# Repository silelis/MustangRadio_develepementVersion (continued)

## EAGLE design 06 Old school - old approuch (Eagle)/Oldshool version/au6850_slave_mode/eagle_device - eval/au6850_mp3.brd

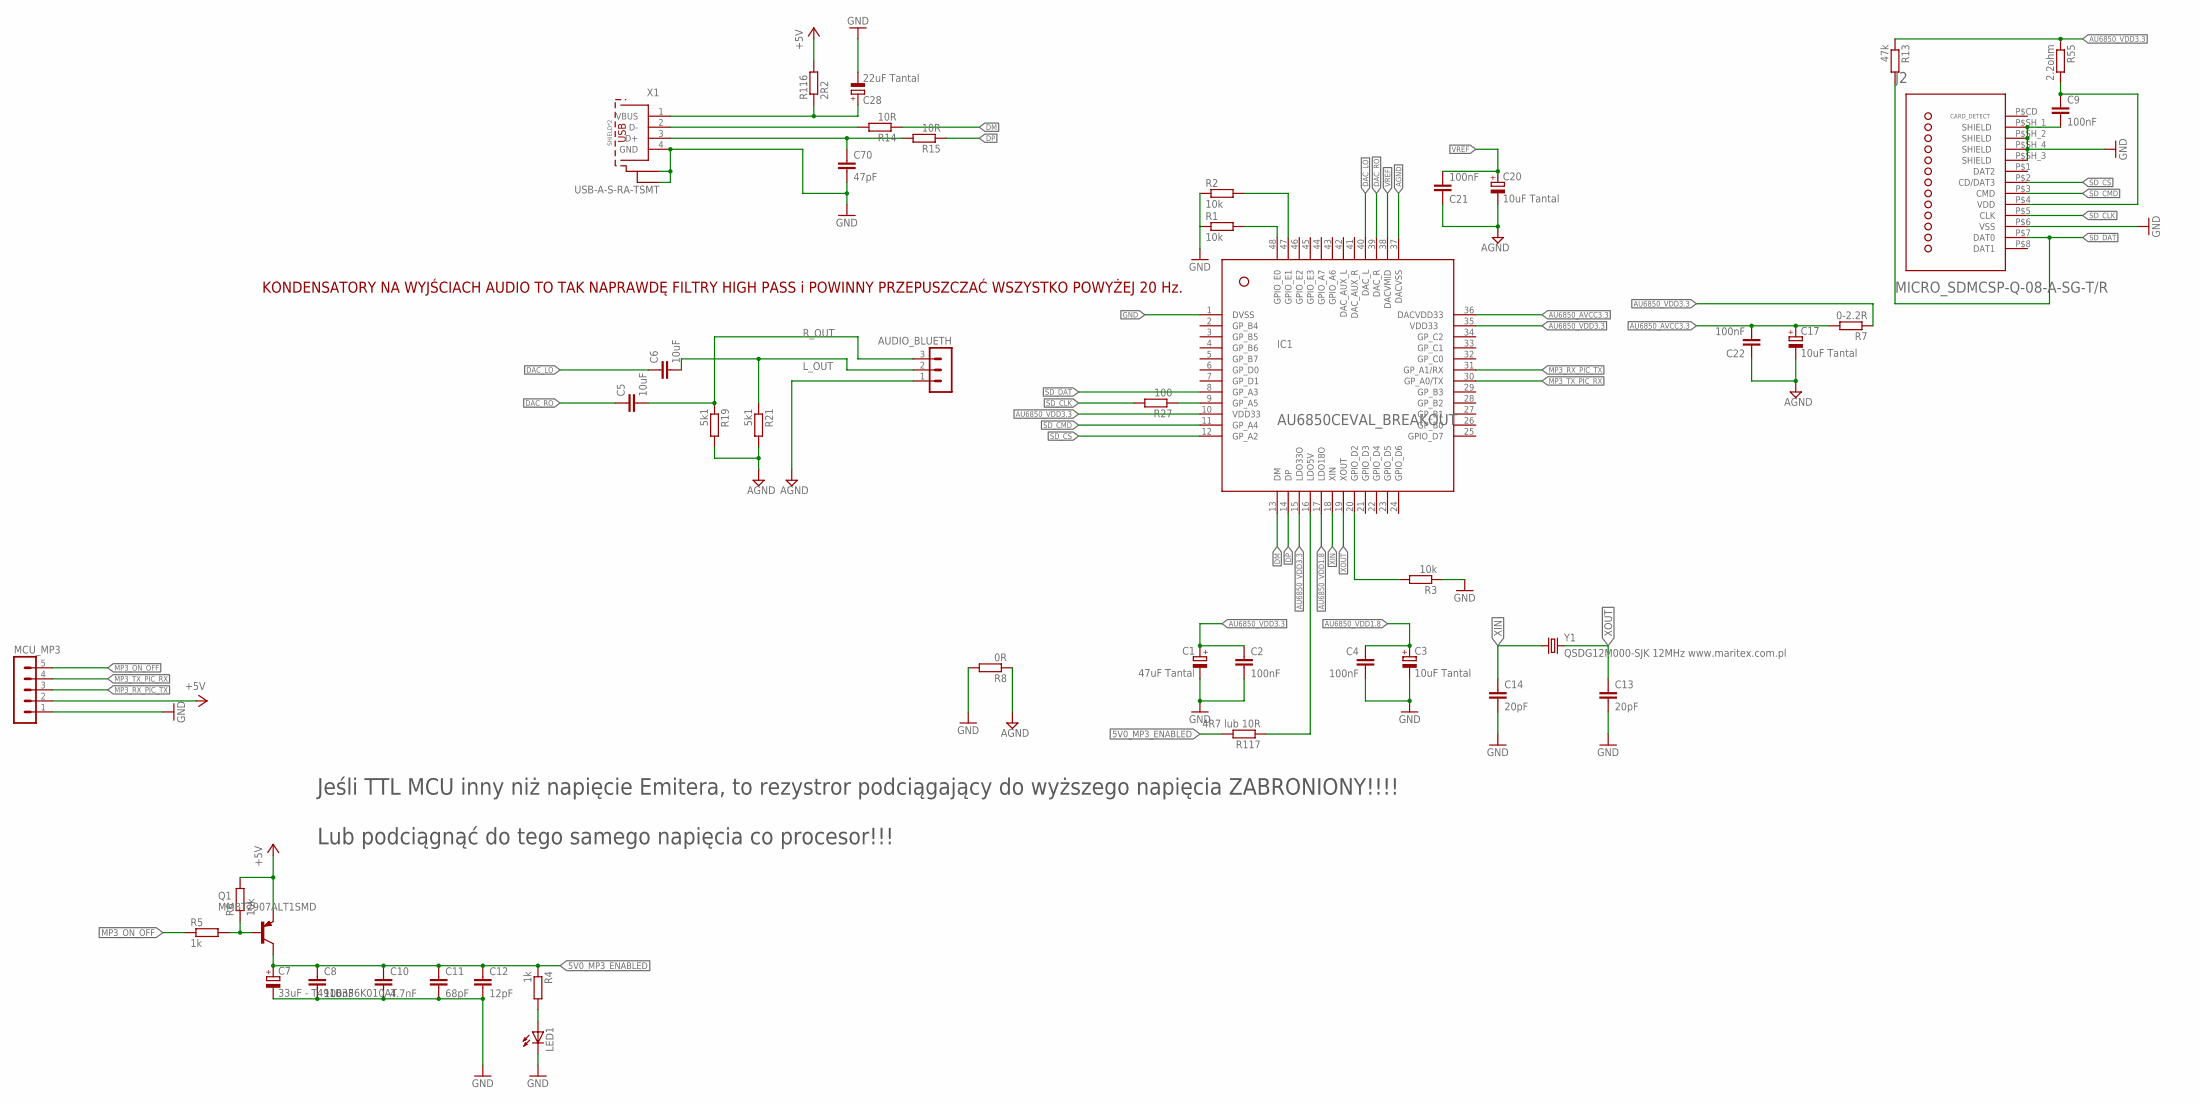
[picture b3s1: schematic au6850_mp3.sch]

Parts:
AUDIO_BLUETH: MA03-1
C1: 47uF Tantal; B/3528-21R; PARTNUM TAJB476K010R
C2, C4, C8, C9, C21, C22: 100nF; C0805
C3: 10uF Tantal; B/3528-21R; PARTNUM TAJA106K010R
C5, C6: 10uF; C0805
C7: 33uF - T491B336K010AT; SMC_B; PARTNUM TAJB336K010R
C10: 4.7nF; C0805
C11: 68pF; C0805
C12: 12pF; C0603K
C13, C14: 20pF; C0805
C17, C20: 10uF Tantal; B/3528-21R
C28: 22uF Tantal; SMC_B; PARTNUM TAJB226M010R
C70: 47pF; C0805
IC1: AU6850CEVAL_BREAKOUT; LQFP48-7BREAKOUT
J2: MICRO_SDMCSP-Q-08-A-SG-T/R; MICRO_SD_8PINS; PARTNUM MCSP-Q-08-A-SG-T/R
LED1: LED3MM
MCU_MP3: MA05-1
Q1: MMBT2907ALT1SMD; SOT23-BEC
R1, R2, R3: 10k; R0805
R4, R5: 1k; M0805
R6: 10k; M0805
R7: 0-2.2R; R0805
R8: 0R; R0805
R13: 47k; R0805
R14, R15: 10R; R0805
R19, R21: 5k1; R0805
R27: 100; R0805
R55: 2.2ohm; R0805
R116: 2R2; R0805
R117: 4R7 lub 10R; R0805
X1: USB-A-S-RA-TSMT
Y1: QSDG12M000-SJK 12MHz www.maritex.com.pl; HC49UP; PARTNUM 12.00M-SMDHC49S

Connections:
5V0_MP3_ENABLED: C7.+, C8.1, C10.1, C11.1, C12.1, Q1.C, R4.1, R117.2
+5V: MCU_MP3.2, Q1.E, R6.2, R116.2
AGND: AUDIO_BLUETH.1, C17.-, C20.-, C21.1, C22.1, IC1.37 (DACVSS), R8.1, R19.2, R21.2
AU6850_AVCC3.3: C17.+, C22.2, IC1.36 (DACVDD33), R7.2
AU6850_VDD1.8: C3.+, C4.1, IC1.17 (LDO18O)
AU6850_VDD3.3: C1.+, C2.1, IC1.10 (VDD33), IC1.15 (LDO33O), IC1.35 (VDD33), R7.1, R13.1, R55.1
DAC_LO: C6.1, IC1.40 (DAC_L)
DAC_RO: C5.1, IC1.39 (DAC_R)
DM: IC1.13 (DM), R14.1
DP: IC1.14 (DP), R15.1
GND: C1.-, C2.2, C3.-, C4.2, C7.-, C8.2, C9.2, C10.2, C11.2, C12.2, C13.2, C14.2, C28.-, C70.2, IC1.1 (DVSS), J2.P$6 (VSS), J2.P$SH_1 (1_GND_PAD), J2.P$SH_2 (2_GND_PAD), J2.P$SH_3 (3_GND_PAD), J2.P$SH_4 (4_GND_PAD), LED1.K (C), MCU_MP3.1, R1.1, R2.1, R3.1, R8.2, X1.4 (GND), X1.5 (SH1), X1.6 (SH2)
L_OUT: AUDIO_BLUETH.2, C6.2, R21.1
MP3_ON_OFF: MCU_MP3.5, R5.1
MP3_RX_PIC_TX: IC1.31 (GP_A1/RX), MCU_MP3.3
MP3_TX_PIC_RX: IC1.30 (GP_A0/TX), MCU_MP3.4
unnamed: LED1.A, R4.2
unnamed: Q1.B, R5.2, R6.1
unnamed: IC1.16 (LDO5V), R117.1
unnamed: IC1.9 (GP_A5), R27.1
unnamed: C28.+, R116.1, X1.1 (VBUS)
unnamed: C70.1, R15.2, X1.3 (D+)
unnamed: R14.2, X1.2 (D-)
unnamed: C9.1, J2.P$4 (VDD), R55.2
R_OUT: AUDIO_BLUETH.3, C5.2, R19.1
SD_CLK: J2.P$5 (CLK), R27.2
SD_CMD: IC1.11 (GP_A4), J2.P$3 (CMD)
SD_CS: IC1.12 (GP_A2), J2.P$2 (CD/DAT3)
SD_DAT: IC1.8 (GP_A3), J2.P$7 (DAT0), R13.2
SLAVE_D2: IC1.20 (GPIO_D2), R3.2
SLAVE_E0: IC1.48 (GPIO_E0), R1.2
SLAVE_E1: IC1.47 (GPIO_E1), R2.2
VREF: C20.+, C21.2, IC1.38 (DACVMID)
XIN: C14.1, IC1.18 (XIN), Y1.1
XOUT: C13.1, IC1.19 (XOUT), Y1.2

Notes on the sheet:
KONDENSATORY NA WYJŚCIACH AUDIO TO TAK NAPRAWDĘ FILTRY HIGH PASS i POWINNY PRZEPUSZCZAĆ WSZYSTKO POWYŻEJ 20 Hz.
Jeśli TTL MCU inny niż napięcie Emitera, to rezystror podciągający do wyższego napięcia ZABRONIONY!!!! Lub podciągnąć do tego samego napięcia co procesor!!!

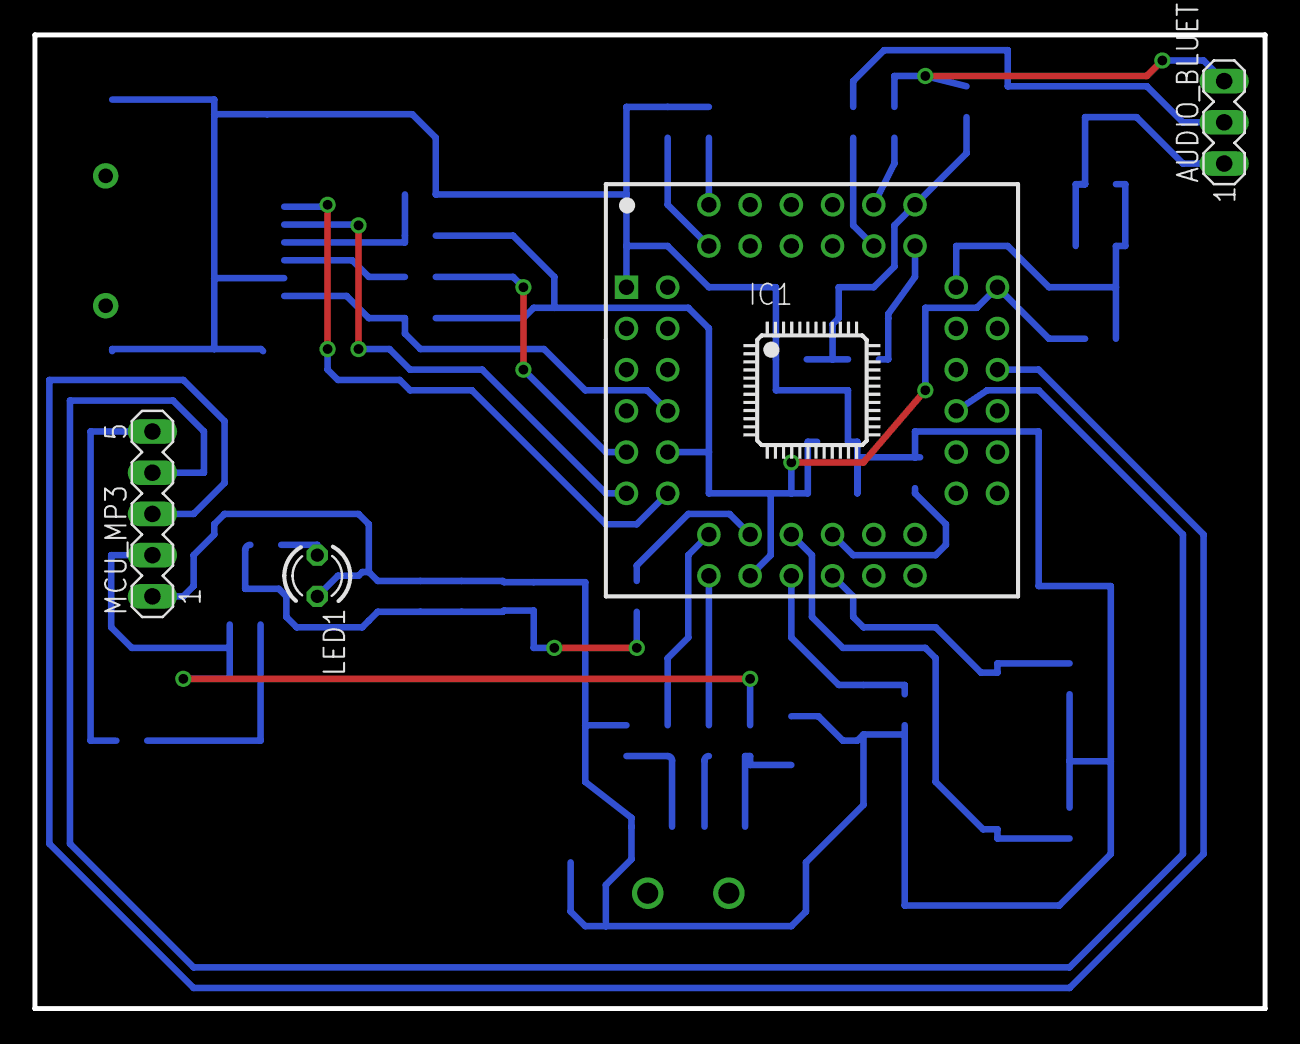
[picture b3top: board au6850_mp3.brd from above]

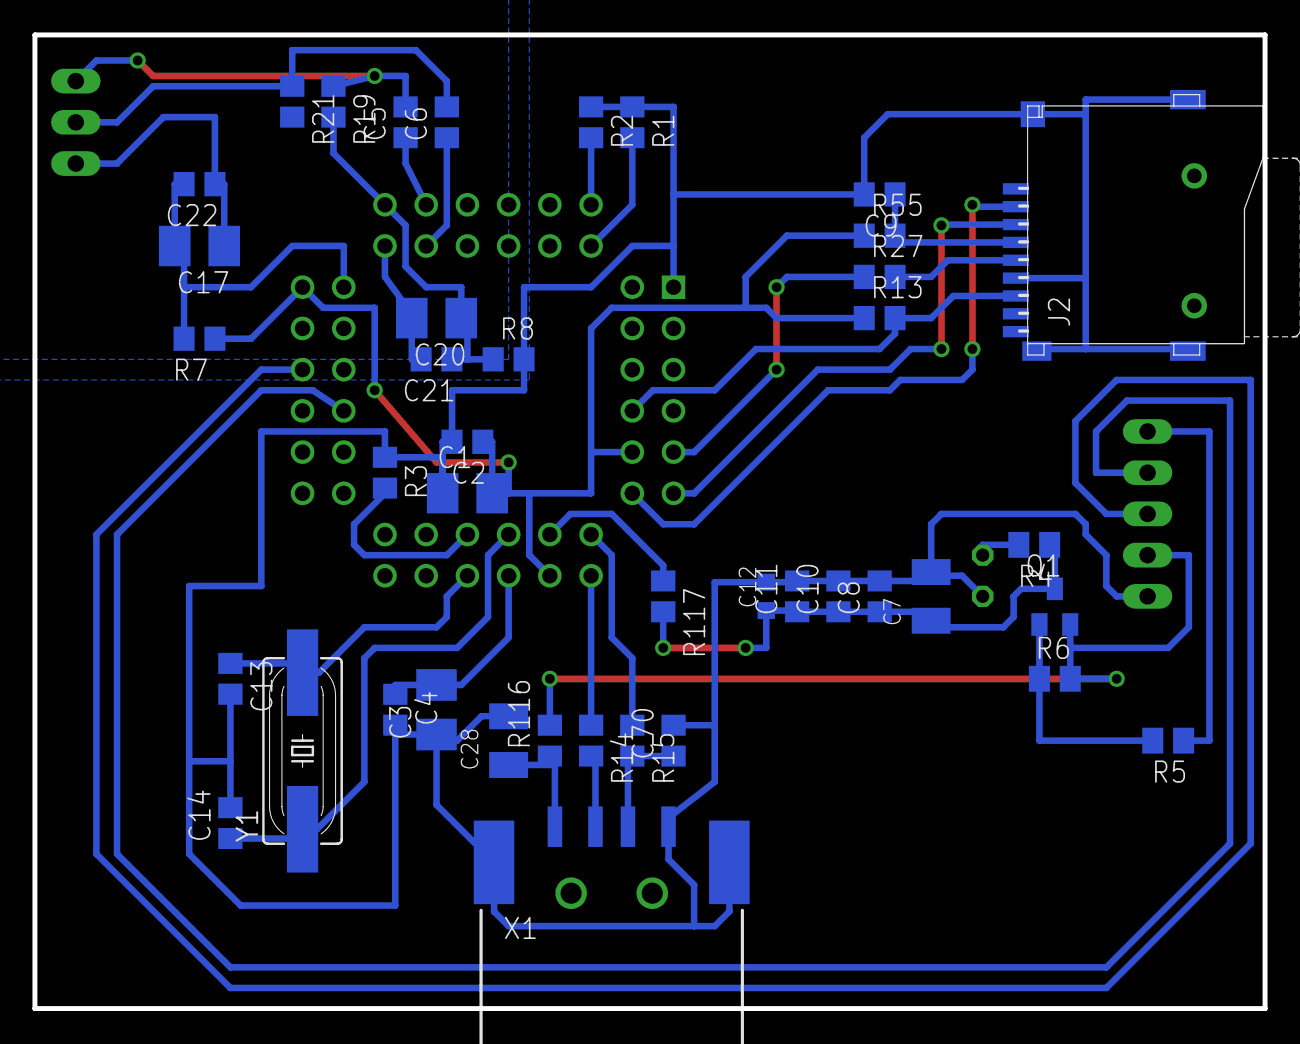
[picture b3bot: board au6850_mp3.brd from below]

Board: 2 copper layers, 75.8 x 60.0 mm, 45 parts (41 on the bottom side), 34 nets.

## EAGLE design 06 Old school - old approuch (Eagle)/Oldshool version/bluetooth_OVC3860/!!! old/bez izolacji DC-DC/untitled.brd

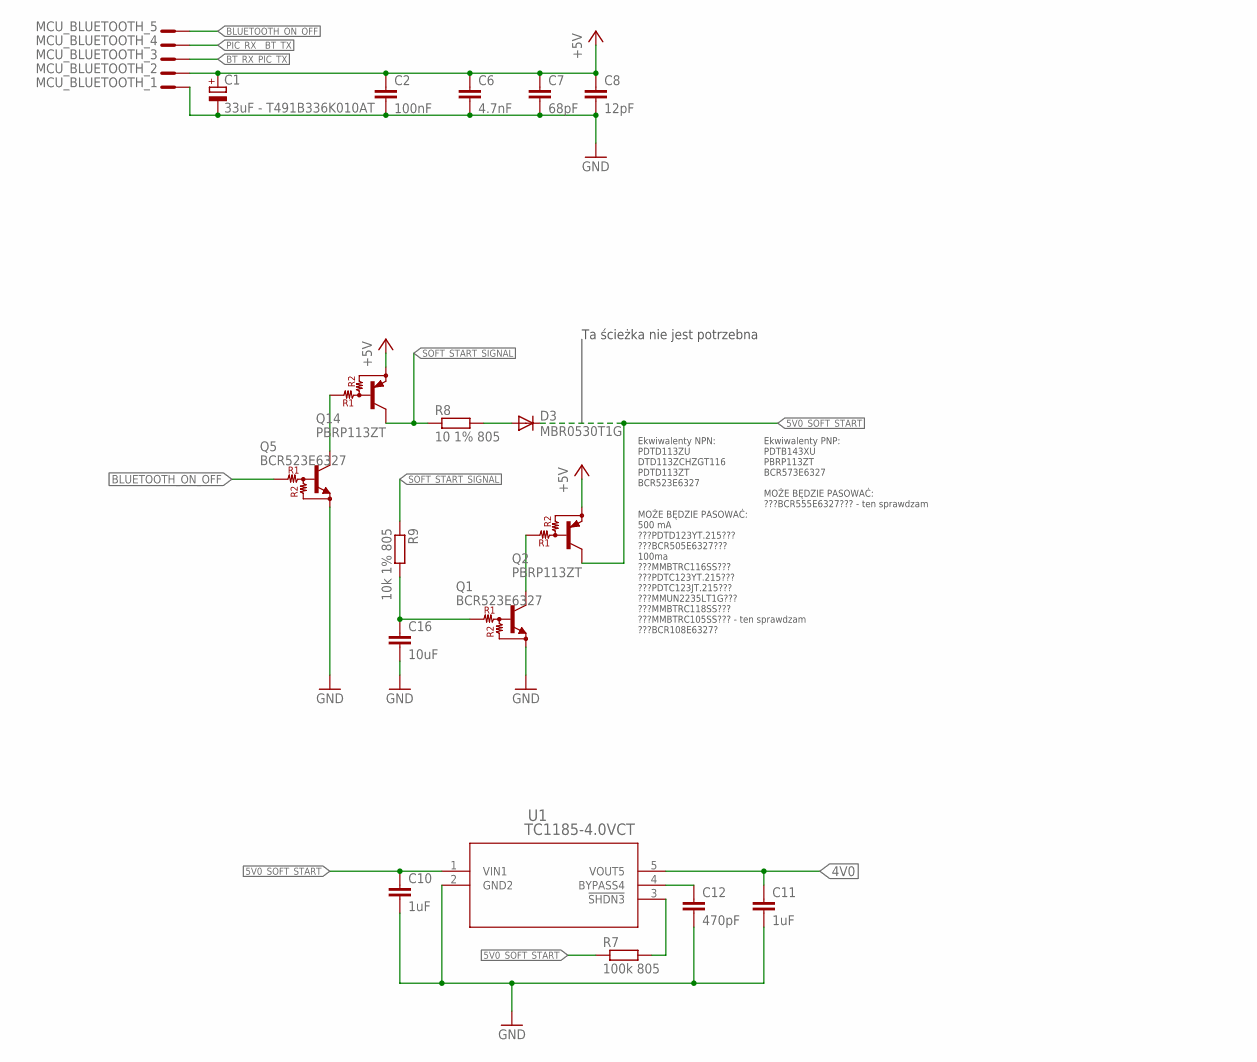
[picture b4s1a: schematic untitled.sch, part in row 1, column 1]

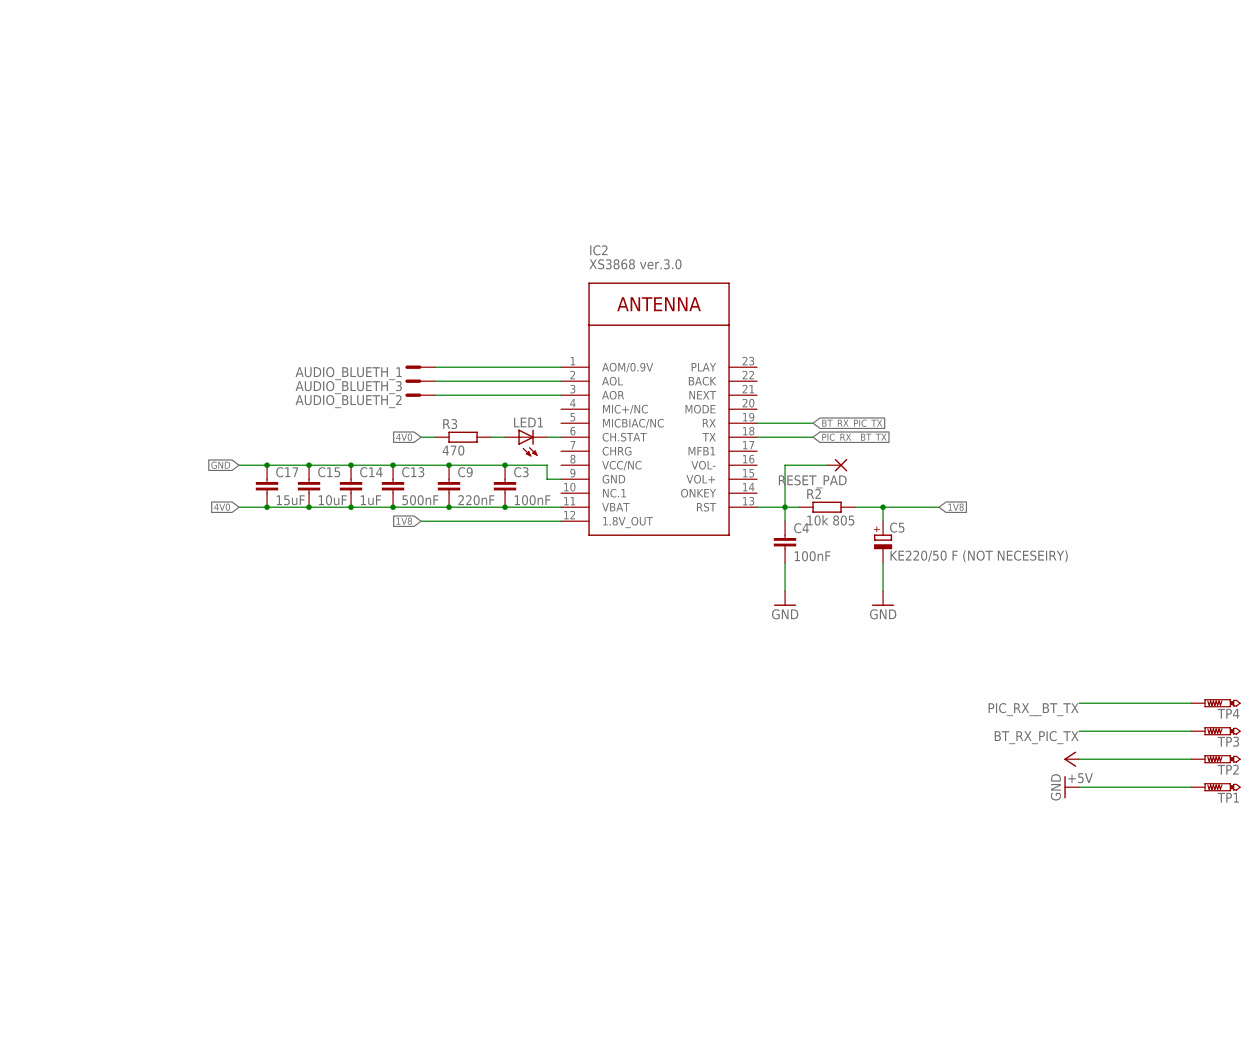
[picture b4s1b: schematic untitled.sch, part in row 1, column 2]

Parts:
AUDIO_BLUETH: JST_3_PIN_B3B-PH-KS; B3B-PH-KS
C1: 33uF - T491B336K010AT; SMC_C
C2, C3, C4: 100nF; C0805
C5: KE220/50 F (NOT NECESEIRY); PANASONIC_G
C6: 4.7nF; C0805
C7: 68pF; C0805
C8: 12pF; C0805
C9: 220nF; C0805
C10, C11, C14: 1uF; C0805
C12: 470pF; C0805
C13: 500nF; C0805
C15, C16: 10uF; C0805
C17: 15uF; C0805
D3: MBR0530T1G; SOD123
IC2: XS3868 ver.3.0; WIRELESS-BLUETOOTH-XS3868
LED1: LEDSML0805; SML0805
MCU_BLUETOOTH: JST_5_PIN_B5B-PH-KS; B5B-PH-KS
Q1, Q5: BCR523E6327; SOT-23
Q2, Q14: PBRP113ZT; SOT-23
R2: 10k 805; M0805
R3: 470; M0805
R7: 100k 805; M0805
R8: 10 1% 805; M0805
R9: 10k 1% 805; M0805
RESET_PAD: SMD2; SMD1,27-2,54
TP1, TP2, TP3, TP4: PTR1B1,27; B1,27
U1: TC1185-4.0VCT; SOT-23-5_MC-M

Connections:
1V8: C5.+, IC2.12 (1.8V_OUT), R2.2
4V0: C3.2, C9.2, C11.1, C13.2, C14.2, C15.2, C17.2, IC2.11 (VBAT), R3.1, U1.5 (VOUT5)
5V0_SOFT_START: C10.1, D3.C, Q2.3 (C), R7.1, U1.1 (VIN1)
+5V: C1.+, C2.1, C6.1, C7.1, C8.1, MCU_BLUETOOTH.P$2, Q2.2 (E), Q14.2 (E), TP2.TP
AUDIO_DIFF_COMMON: AUDIO_BLUETH.P$1, IC2.1 (AOM/0.9V)
BLUETOOTH_ON_OFF: MCU_BLUETOOTH.P$5, Q5.1 (B)
BTOUT_LEFT: AUDIO_BLUETH.P$2, IC2.3 (AOR)
BTOUT_RIGHT: AUDIO_BLUETH.P$3, IC2.2 (AOL)
BT_LED: IC2.6 (CH.STAT), LED1.C
BT_RX_PIC_TX: IC2.19 (RX), MCU_BLUETOOTH.P$3, TP3.TP
GND: C1.-, C2.2, C3.1, C4.2, C5.-, C6.2, C7.2, C8.2, C9.1, C10.2, C11.2, C12.2, C13.1, C14.1, C15.1, C16.2, C17.1, IC2.9 (GND), MCU_BLUETOOTH.P$1, Q1.2 (E), Q5.2 (E), TP1.TP, U1.2 (GND2)
unnamed: C12.1, U1.4 (BYPASS4)
unnamed: LED1.A, R3.2
unnamed: R7.2, U1.3 (!SHDN3)
unnamed: Q5.3 (C), Q14.1 (B)
unnamed: C16.1, Q1.1 (B), R9.2
unnamed: Q1.3 (C), Q2.1 (B)
unnamed: D3.A, R8.2
PIC_RX__BT_TX: IC2.18 (TX), MCU_BLUETOOTH.P$4, TP4.TP
RST: C4.1, IC2.13 (RST), R2.1, RESET_PAD.1
SOFT_START_SIGNAL: Q14.3 (C), R8.1, R9.1

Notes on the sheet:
Ekwiwalenty PNP: PDTB143XU PBRP113ZT BCR573E6327 MOŻE BĘDZIE PASOWAĆ: ???BCR555E6327??? - ten sprawdzam
Ekwiwalenty NPN: PDTD113ZU DTD113ZCHZGT116 PDTD113ZT BCR523E6327 MOŻE BĘDZIE PASOWAĆ: 500 mA ???PDTD123YT.215??? ???BCR505E6327??? 100ma ???MMBTRC116SS??? ???PDTC123YT.215??? ???PDTC123JT.215??? ???MMUN2235LT1G??? ???MMBTRC118SS??? ???MMBTRC105SS??? - ten sprawdzam ???BCR108E6327?
Ta ścieżka nie jest potrzebna

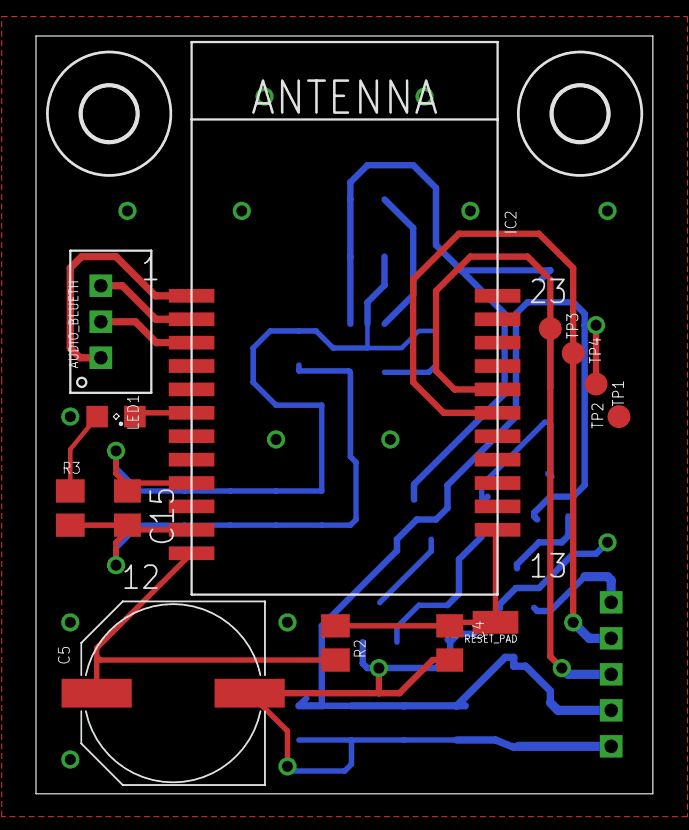
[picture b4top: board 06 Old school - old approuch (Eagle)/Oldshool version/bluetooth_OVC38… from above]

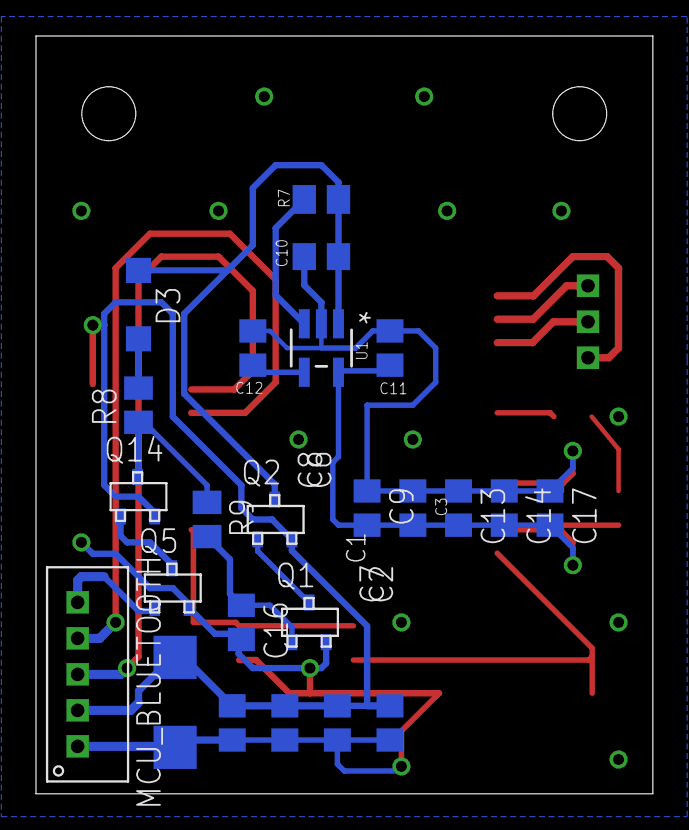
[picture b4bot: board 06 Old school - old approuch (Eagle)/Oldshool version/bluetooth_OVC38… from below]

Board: 2 copper layers, 34.3 x 42.1 mm, 39 parts (24 on the bottom side), 21 nets.

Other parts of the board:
U$2, U$3: 3,0

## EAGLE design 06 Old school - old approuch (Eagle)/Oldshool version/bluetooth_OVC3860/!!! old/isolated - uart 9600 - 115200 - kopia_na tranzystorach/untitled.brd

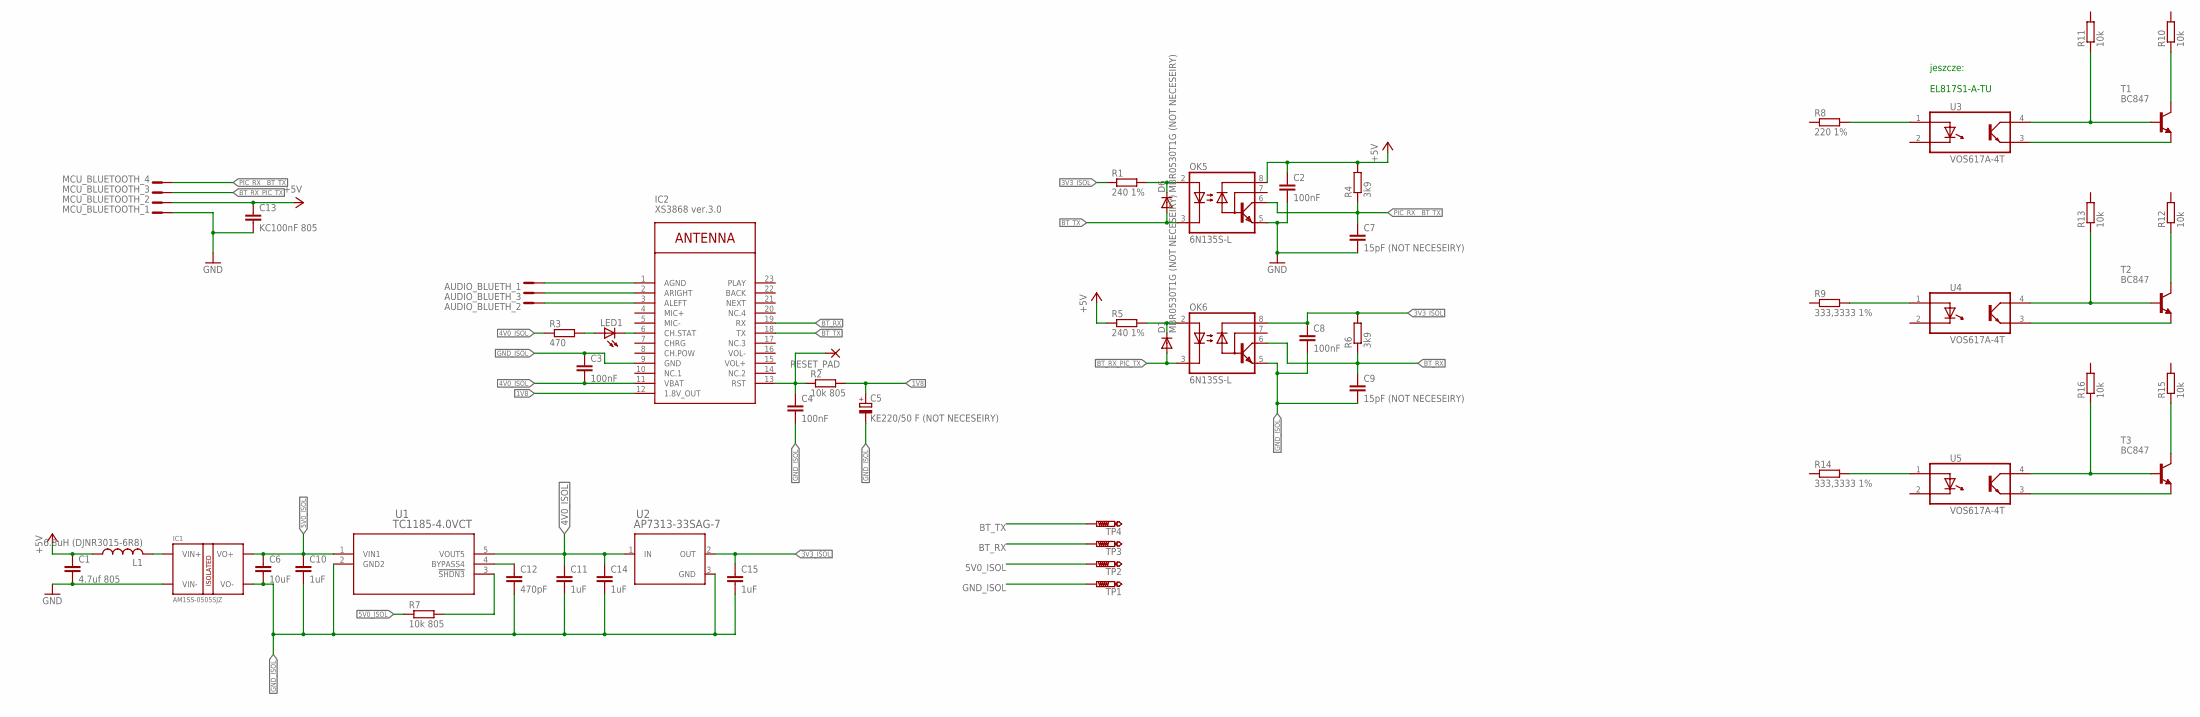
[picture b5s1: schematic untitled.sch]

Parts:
AUDIO_BLUETH: JST_3_PIN_B3B-PH-KS; B3B-PH-KS
C1: 4.7uf 805; C0805
C2, C3, C4, C8: 100nF; C0805
C5: KE220/50 F (NOT NECESEIRY); PANASONIC_G
C6: 10uF; C0805
C7, C9: 15pF (NOT NECESEIRY); C0805
C10, C11, C14, C15: 1uF; C0805
C12: 470pF; C0805
C13: KC100nF 805; C0805
D1, D6: MBR0530T1G (NOT NECESEIRY); SOD123
IC1: AM1SS-0505SJZ; SIP4
IC2: XS3868 ver.3.0; WIRELESS-BLUETOOTH-XS3868
L1: 6.8uH (DJNR3015-6R8); L3230M
LED1: LEDSMART-LED; SMART-LED
MCU_BLUETOOTH: JST_4_PIN_B4B-PH-KS; B4B-PH-KS
OK5, OK6: 6N135S-L; DIL8-SMD
R1, R5: 240 1%; M0805
R2, R7: 10k 805; M0805
R3: 470; M0805
R4, R6: 3k9; M0805
R8: 220 1%; M0805
R9, R14: 333,3333 1%; M0805
R10, R11, R12, R13, R15, R16: 10k; M0805
RESET_PAD: SMD2; SMD1,27-2,54
T1, T2, T3: BC847; SOT23
TP1, TP2, TP3, TP4: PTR1B1,27; B1,27
U1: TC1185-4.0VCT; SOT-23-5_MC-M
U2: AP7313-33SAG-7; SOT-23
U3, U4, U5: VOS617A-4T; SOIC127P700X210-4N

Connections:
1V8: C5.+, IC2.12 (1.8V_OUT), R2.2
3V3_ISOL: C8.1, C15.1, OK6.8 (VCC), R1.1, R6.2, U2.2 (OUT)
4V0_ISOL: C3.2, C11.1, C14.1, IC2.11 (VBAT), R3.1, U1.5 (VOUT5), U2.1 (IN)
5V0_ISOL: C6.1, C10.1, IC1.P$4 (VO+), R7.1, TP2.TP, U1.1 (VIN1)
+5V: C1.1, C2.1, C13.1, L1.1, MCU_BLUETOOTH.P$2, OK5.8 (VCC), R4.2, R5.1
AGND: AUDIO_BLUETH.P$1, IC2.1 (AGND)
BTOUT_LEFT: AUDIO_BLUETH.P$2, IC2.3 (ALEFT)
BTOUT_RIGHT: AUDIO_BLUETH.P$3, IC2.2 (ARIGHT)
BT_LED: IC2.6 (CH.STAT), LED1.B (C)
BT_RX: C9.1, IC2.19 (RX), OK6.6 (VO), R6.1, TP3.TP
BT_RX_PIC_TX: D1.A, MCU_BLUETOOTH.P$3, OK6.3 (C)
BT_TX: D6.A, IC2.18 (TX), OK5.3 (C), TP4.TP
GND: C1.2, C2.2, C7.2, C13.2, IC1.P$1 (VIN-), MCU_BLUETOOTH.P$1, OK5.5 (GND)
GND_ISOL: C3.1, C4.2, C5.-, C6.2, C8.2, C9.2, C10.2, C11.2, C12.2, C14.2, C15.2, IC1.P$3 (VO-), IC2.9 (GND), OK6.5 (GND), TP1.TP, U1.2 (GND2), U2.3 (GND)
unnamed: IC1.P$2 (VIN+), L1.2
unnamed: D6.C, OK5.2 (A), R1.2
unnamed: D1.C, OK6.2 (A), R5.2
unnamed: C12.1, U1.4 (BYPASS4)
unnamed: LED1.A, R3.2
unnamed: R7.2, U1.3 (!SHDN3)
unnamed: R8.2, U3.1 (A)
unnamed: R9.2, U4.1 (A)
unnamed: R10.1, T1.3 (C)
unnamed: R11.1, T1.1 (B), U3.4 (CO)
unnamed: T1.2 (E), U3.3 (E)
unnamed: R12.1, T2.3 (C)
unnamed: R13.1, T2.1 (B), U4.4 (CO)
unnamed: T2.2 (E), U4.3 (E)
unnamed: R14.2, U5.1 (A)
unnamed: R15.1, T3.3 (C)
unnamed: R16.1, T3.1 (B), U5.4 (CO)
unnamed: T3.2 (E), U5.3 (E)
PIC_RX__BT_TX: C7.1, MCU_BLUETOOTH.P$4, OK5.6 (VO), R4.1
RST: C4.1, IC2.13 (RST), R2.1, RESET_PAD.1

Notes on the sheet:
jeszcze: EL817S1-A-TU

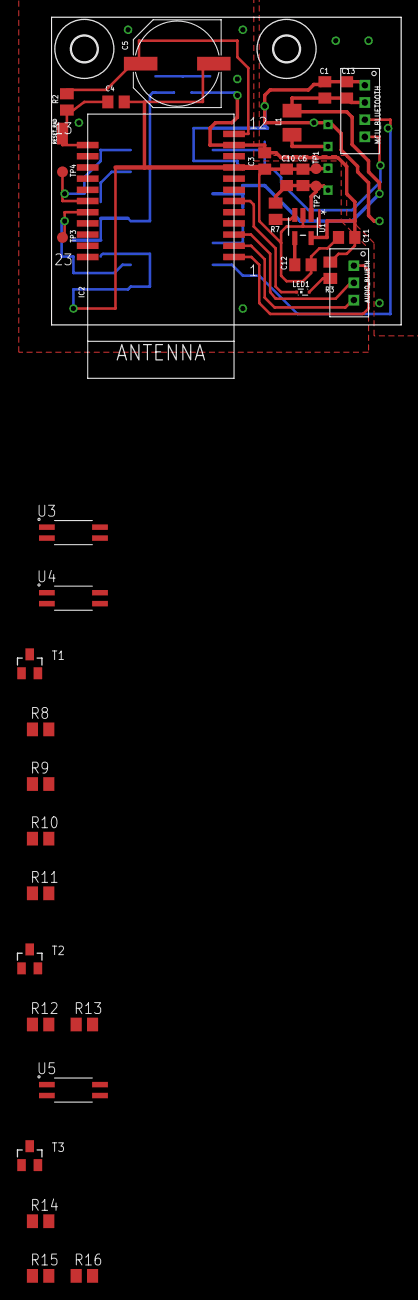
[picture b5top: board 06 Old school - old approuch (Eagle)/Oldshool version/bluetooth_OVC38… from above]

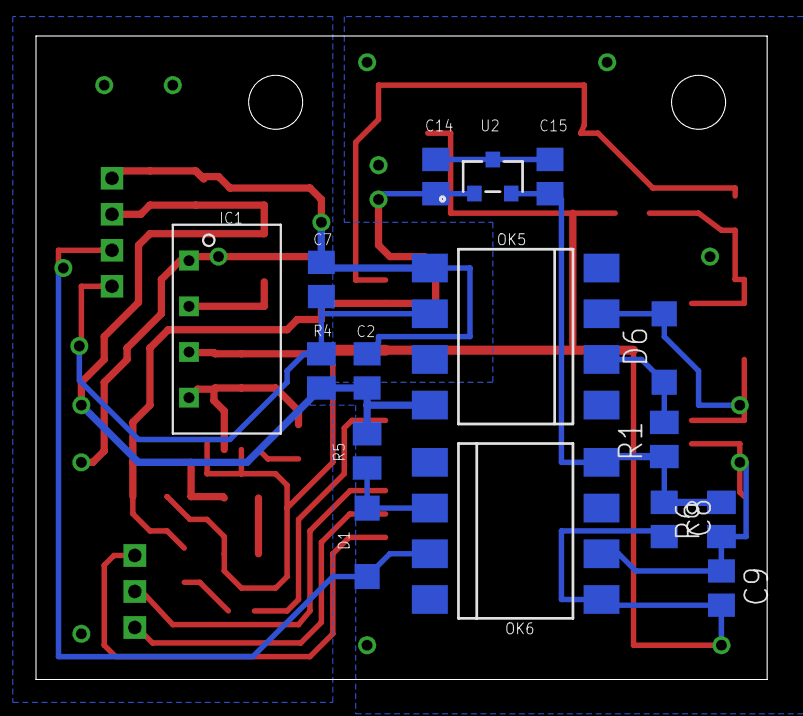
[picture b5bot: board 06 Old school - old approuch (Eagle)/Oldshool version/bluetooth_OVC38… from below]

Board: 2 copper layers, 40.6 x 35.8 mm, 56 parts (16 on the bottom side), 34 nets.

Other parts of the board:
U$2, U$3: 3,0
